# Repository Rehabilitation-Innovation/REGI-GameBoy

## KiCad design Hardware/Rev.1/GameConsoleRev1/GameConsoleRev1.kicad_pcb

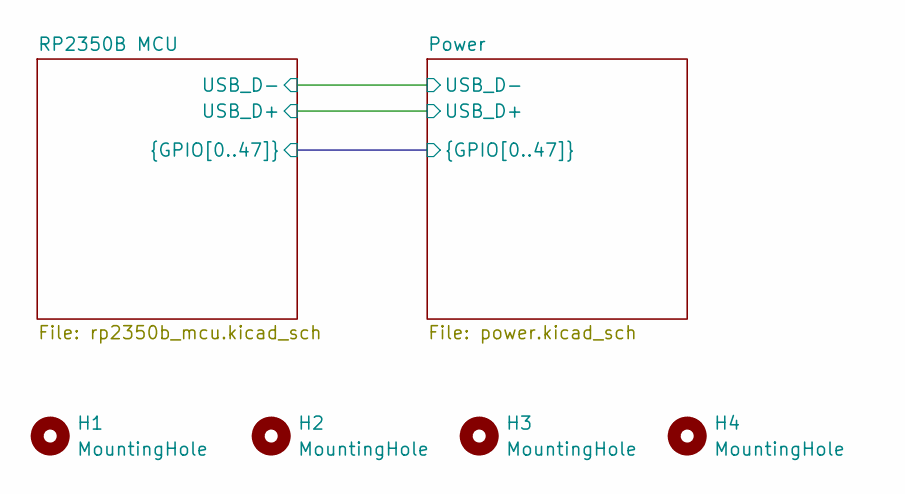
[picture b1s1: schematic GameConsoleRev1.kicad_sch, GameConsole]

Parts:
H1, H2, H3, H4: MountingHole; MountingHole_3.2mm_M3_Pad_Via

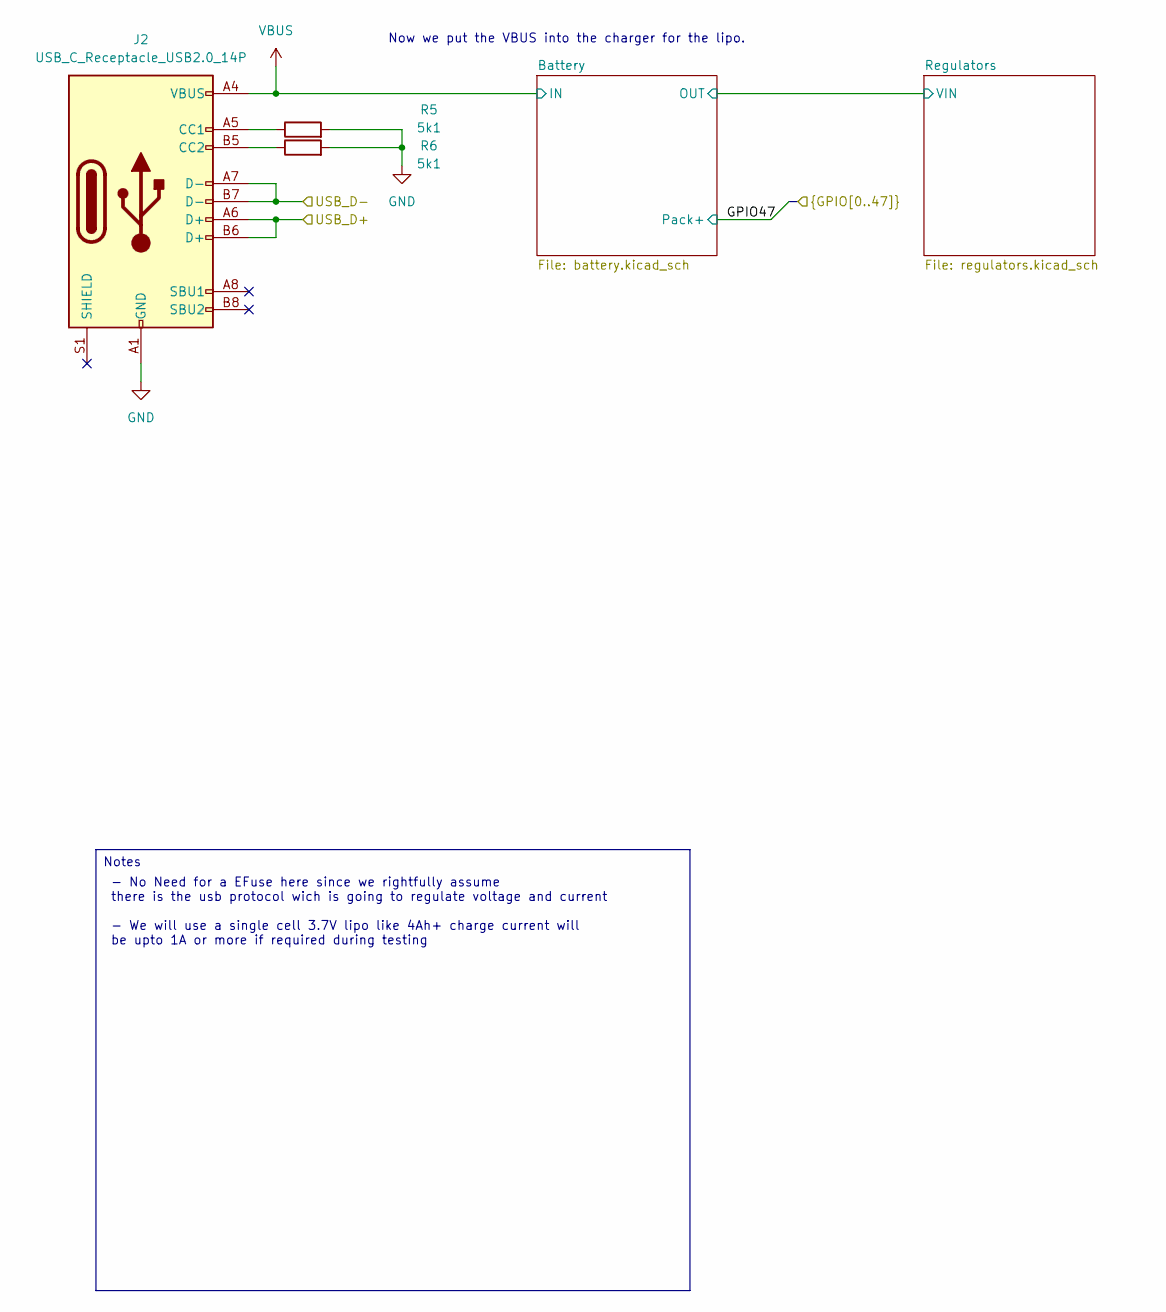
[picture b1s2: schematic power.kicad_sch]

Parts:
J2: USB_C_Receptacle_USB2.0_14P; USB_C_Receptacle_G-Switch_GT-USB-7010ASV; LCSC C2988369
R5, R6: 5k1; R_0402_1005Metric

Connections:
/Power/USB_D+: J2.A6 (D+), J2.B6 (D+); also elsewhere on the board
/Power/USB_D-: J2.A7 (D-), J2.B7 (D-); also elsewhere on the board
GND: J2.A1 (GND), J2.A12 (GND), J2.B1 (GND), J2.B12 (GND), R5.2, R6.2; also elsewhere on the board
unnamed: J2.A5 (CC1), R5.1
unnamed: J2.B5 (CC2), R6.1
VBUS: J2.A4 (VBUS), J2.A9 (VBUS), J2.B4 (VBUS), J2.B9 (VBUS); also elsewhere on the board

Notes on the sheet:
- No Need for a EFuse here since we rightfully assume there is the usb protocol wich is going to regulate voltage and current - We will use a single cell 3.7V lipo like 4Ah+ charge current will be upto 1A or more if required during testing
Now we put the VBUS into the charger for the lipo.
Notes

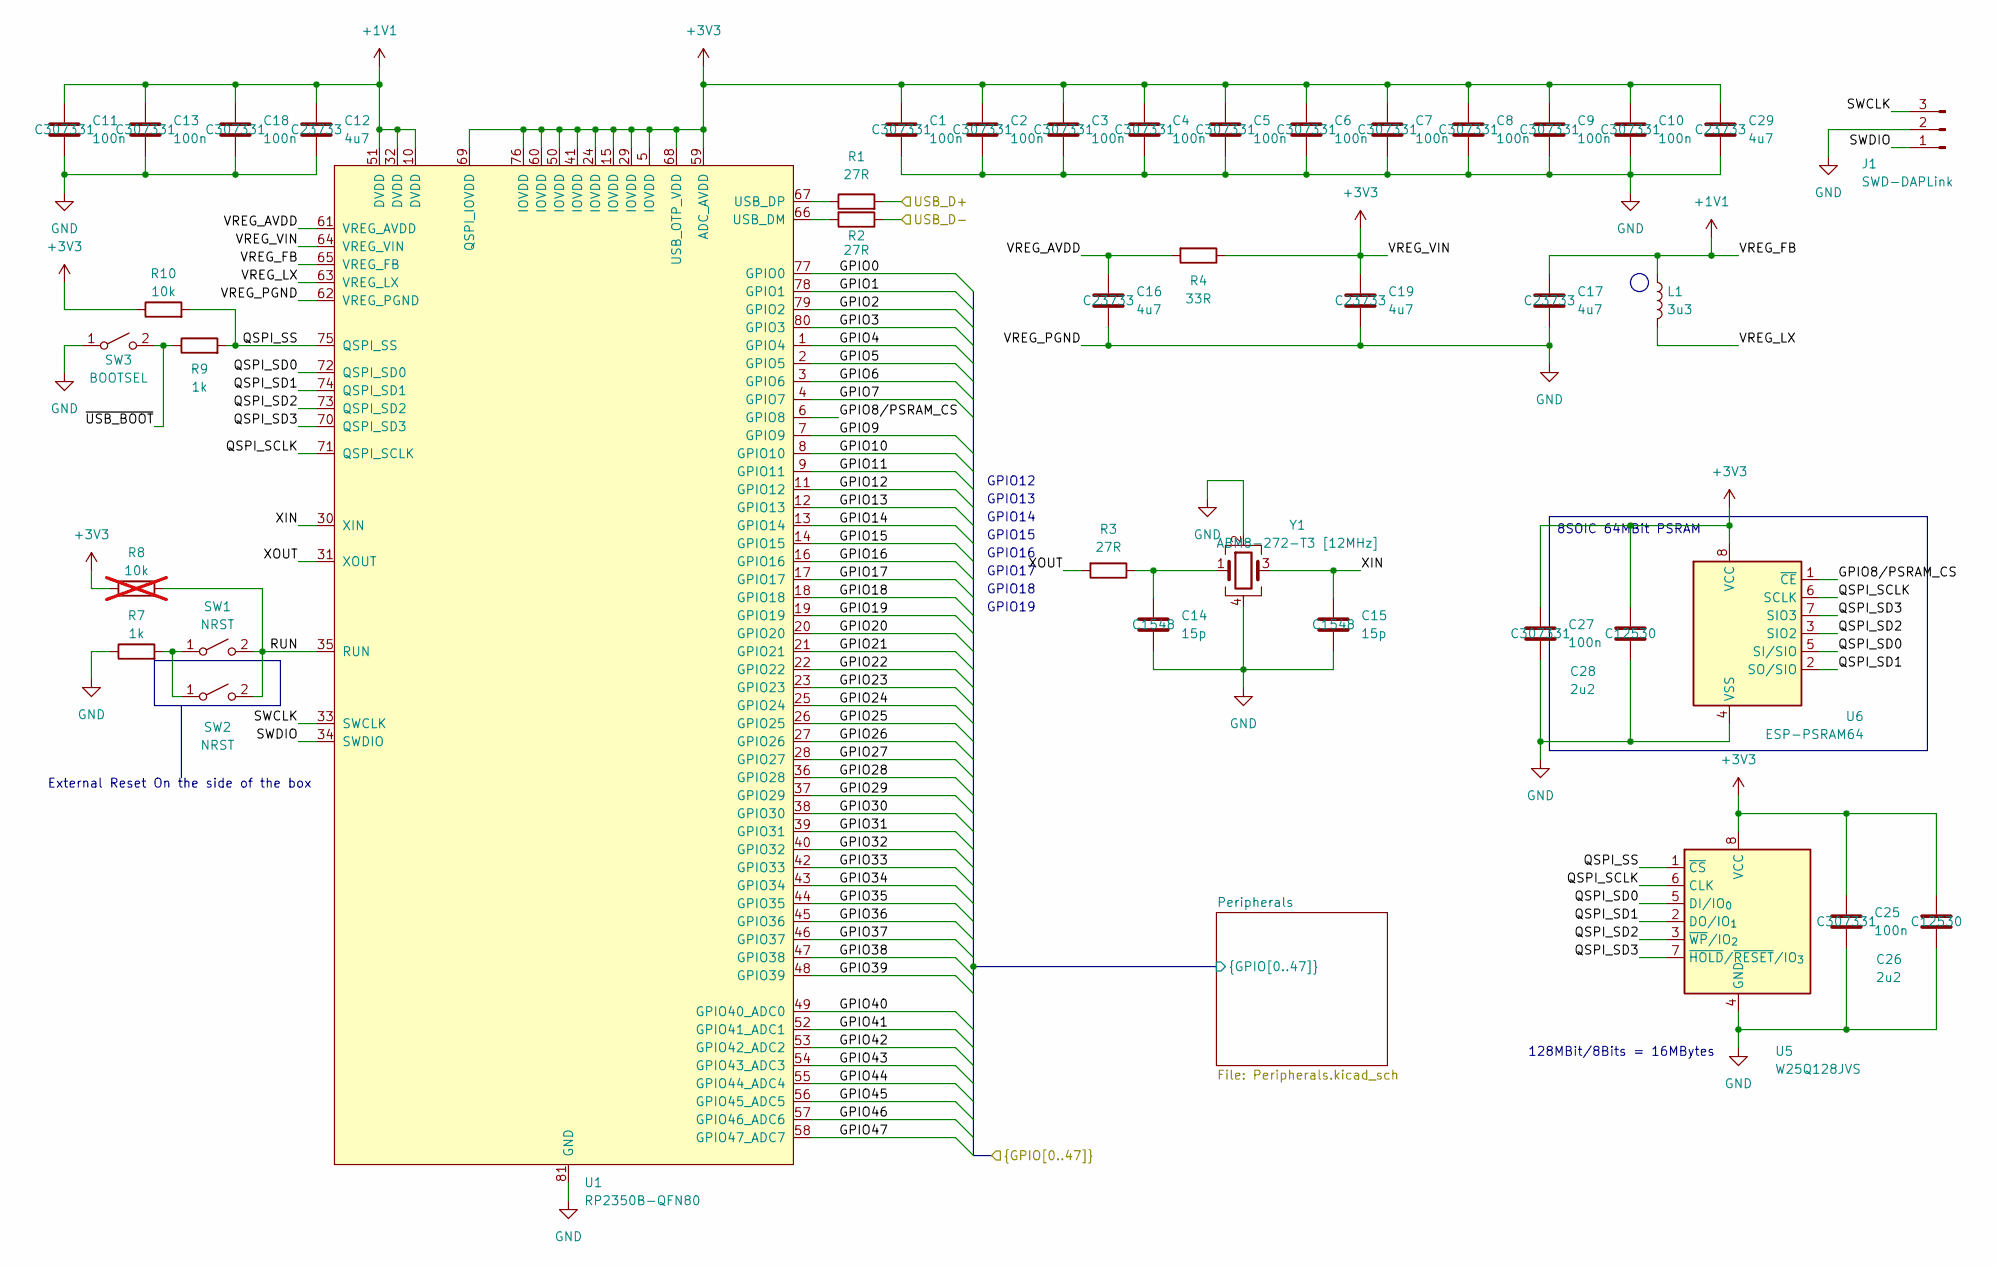
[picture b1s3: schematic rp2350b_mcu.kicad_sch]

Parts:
C1, C2, C3, C4, C5, C6, C7, C8, C9, C10, C11, C13, C18, C25, C27: 100n; C_0402_1005Metric; LCSC C307331
C12, C16, C17, C19, C29: 4u7; C_0402_1005Metric; LCSC C23733
C14, C15: 15p; C_0402_1005Metric; LCSC C1548
C26, C28: 2u2; C_0402_1005Metric; LCSC C12530
J1: SWD-DAPLink; PinHeader_1x03_P2.54mm_Vertical
L1: 3u3; AOTA-B201610S3R3-101-T; LCSC C42411119
R1, R2, R3: 27R; C_0402_1005Metric
R4: 33R; C_0402_1005Metric
R7, R9: 1k; R_0805_2012Metric
R8: 10k; R_0805_2012Metric; not fitted
R10: 10k; R_0805_2012Metric
SW1: NRST; SW_Push_1P1T_NO_Vertical_Wuerth_434133025816
SW2: NRST; SW_Tactile_SPST_Angled_PTS645Vx58-2LFS
SW3: BOOTSEL; SW_Push_1P1T_NO_Vertical_Wuerth_434133025816
U1: RP2350B-QFN80; RP2350B_QFN-80_EP_10.573x10.573_Pitch0.4mm; LCSC C42415655
U5: W25Q128JVS; SOIC-8_5.3x5.3mm_P1.27mm
U6: ESP-PSRAM64; SOIC-8_3.9x4.9mm_P1.27mm
Y1: ABM8-272-T3 [12MHz]; Crystal_SMD_3225-4Pin_3.2x2.5mm; LCSC C20625731

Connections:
+1V1: C11.1, C12.1, C13.1, C17.1, C18.1, L1.1, U1.10 (DVDD), U1.32 (DVDD), U1.51 (DVDD), U1.65 (VREG_FB)
+3V3: C1.1, C2.1, C3.1, C4.1, C5.1, C6.1, C7.1, C8.1, C9.1, C10.1, C19.1, C25.1, C26.1, C27.1, C28.1, C29.1, R4.1, R8.1, R10.1, U1.5 (IOVDD), U1.15 (IOVDD), U1.24 (IOVDD), U1.29 (IOVDD), U1.41 (IOVDD), U1.50 (IOVDD), U1.59 (ADC_AVDD), U1.60 (IOVDD), U1.64 (VREG_VIN), U1.68 (USB_OTP_VDD), U1.69 (QSPI_IOVDD), U1.76 (IOVDD), U5.8 (VCC), U6.8 (VCC); also elsewhere on the board
/Power/GPIO0: U1.77 (GPIO0); also elsewhere on the board
/Power/GPIO1: U1.78 (GPIO1); also elsewhere on the board
/Power/GPIO2: U1.79 (GPIO2); also elsewhere on the board
/Power/GPIO3: U1.80 (GPIO3); also elsewhere on the board
/Power/GPIO4: U1.1 (GPIO4); also elsewhere on the board
/Power/GPIO5: U1.2 (GPIO5); also elsewhere on the board
/Power/GPIO6: U1.3 (GPIO6); also elsewhere on the board
/Power/GPIO7: U1.4 (GPIO7); also elsewhere on the board
/Power/GPIO9: U1.7 (GPIO9); also elsewhere on the board
/Power/GPIO10: U1.8 (GPIO10); also elsewhere on the board
/Power/GPIO11: U1.9 (GPIO11); also elsewhere on the board
/Power/GPIO12: U1.11 (GPIO12); also elsewhere on the board
/Power/GPIO13: U1.12 (GPIO13); also elsewhere on the board
/Power/GPIO14: U1.13 (GPIO14); also elsewhere on the board
/Power/GPIO15: U1.14 (GPIO15); also elsewhere on the board
/Power/GPIO16: U1.16 (GPIO16); also elsewhere on the board
/Power/GPIO17: U1.17 (GPIO17); also elsewhere on the board
/Power/GPIO18: U1.18 (GPIO18); also elsewhere on the board
/Power/GPIO19: U1.19 (GPIO19); also elsewhere on the board
/Power/GPIO20: U1.20 (GPIO20); also elsewhere on the board
/Power/GPIO21: U1.21 (GPIO21); also elsewhere on the board
/Power/GPIO22: U1.22 (GPIO22); also elsewhere on the board
/Power/GPIO23: U1.23 (GPIO23); also elsewhere on the board
/Power/GPIO24: U1.25 (GPIO24); also elsewhere on the board
/Power/GPIO25: U1.26 (GPIO25); also elsewhere on the board
/Power/GPIO26: U1.27 (GPIO26); also elsewhere on the board
/Power/GPIO27: U1.28 (GPIO27); also elsewhere on the board
/Power/GPIO28: U1.36 (GPIO28); also elsewhere on the board
/Power/GPIO29: U1.37 (GPIO29); also elsewhere on the board
/Power/GPIO30: U1.38 (GPIO30); also elsewhere on the board
/Power/GPIO31: U1.39 (GPIO31); also elsewhere on the board
/Power/GPIO32: U1.40 (GPIO32); also elsewhere on the board
/Power/GPIO33: U1.42 (GPIO33); also elsewhere on the board
/Power/GPIO34: U1.43 (GPIO34); also elsewhere on the board
/Power/GPIO35: U1.44 (GPIO35); also elsewhere on the board
/Power/GPIO36: U1.45 (GPIO36); also elsewhere on the board
/Power/GPIO37: U1.46 (GPIO37); also elsewhere on the board
/Power/GPIO38: U1.47 (GPIO38); also elsewhere on the board
/Power/GPIO39: U1.48 (GPIO39); also elsewhere on the board
/Power/GPIO40: U1.49 (GPIO40_ADC0); also elsewhere on the board
/Power/GPIO41: U1.52 (GPIO41_ADC1); also elsewhere on the board
/Power/GPIO42: U1.53 (GPIO42_ADC2); also elsewhere on the board
/Power/GPIO43: U1.54 (GPIO43_ADC3); also elsewhere on the board
/Power/GPIO44: U1.55 (GPIO44_ADC4); also elsewhere on the board
/Power/GPIO45: U1.56 (GPIO45_ADC5); also elsewhere on the board
/Power/GPIO46: U1.57 (GPIO46_ADC6); also elsewhere on the board
/Power/GPIO47: U1.58 (GPIO47_ADC7); also elsewhere on the board
/Power/USB_D+: R1.2; also elsewhere on the board
/Power/USB_D-: R2.1; also elsewhere on the board
/RP2350B MCU/GPIO8/PSRAM_CS: U1.6 (GPIO8), U6.1 (~CE)
/RP2350B MCU/QSPI_SCLK: U1.71 (QSPI_SCLK), U5.6 (CLK), U6.6 (SCLK)
/RP2350B MCU/QSPI_SD0: U1.72 (QSPI_SD0), U5.5 (DI/IO_{0}), U6.5 (SI/SIO)
/RP2350B MCU/QSPI_SD1: U1.74 (QSPI_SD1), U5.2 (DO/IO_{1}), U6.2 (SO/SIO)
/RP2350B MCU/QSPI_SD2: U1.73 (QSPI_SD2), U5.3 (~WP/IO_{2}), U6.3 (SIO2)
/RP2350B MCU/QSPI_SD3: U1.70 (QSPI_SD3), U5.7 (~HOLD/~RESET/IO_{3}), U6.7 (SIO3)
/RP2350B MCU/QSPI_SS: R9.2, R10.2, U1.75 (QSPI_SS), U5.1 (~CS)
/RP2350B MCU/RUN: R8.2, SW1.2 (B), SW2.2 (B), U1.35 (RUN)
/RP2350B MCU/SWCLK: J1.3, U1.33 (SWCLK)
/RP2350B MCU/SWDIO: J1.1, U1.34 (SWDIO)
/RP2350B MCU/VREG_AVDD: C16.1, R4.2, U1.61 (VREG_AVDD)
/RP2350B MCU/VREG_LX: L1.2, U1.63 (VREG_LX)
/RP2350B MCU/XIN: C15.1, U1.30 (XIN), Y1.3
/RP2350B MCU/XOUT: R3.2, U1.31 (XOUT)
/RP2350B MCU/~USB_BOOT: R9.1, SW3.2 (B)
GND: C1.2, C2.2, C3.2, C4.2, C5.2, C6.2, C7.2, C8.2, C9.2, C10.2, C11.2, C12.2, C13.2, C14.2, C15.2, C16.2, C17.2, C18.2, C19.2, C25.2, C26.2, C27.2, C28.2, C29.2, J1.2, R7.1, SW3.1 (A), U1.62 (VREG_PGND), U1.81 (GND), U5.4 (GND), U6.4 (VSS), Y1.2, Y1.4; also elsewhere on the board
unnamed: C14.1, R3.1, Y1.1
unnamed: R7.2, SW1.1 (A), SW2.1 (A)
unnamed: R2.2, U1.66 (USB_DM)
unnamed: R1.1, U1.67 (USB_DP)

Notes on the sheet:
GPIO15
GPIO19
GPIO16
GPIO14
GPIO17
128MBit/8Bits = 16MBytes
GPIO18
External Reset On the side of the box
GPIO12
GPIO13
8SOIC 64MBit PSRAM

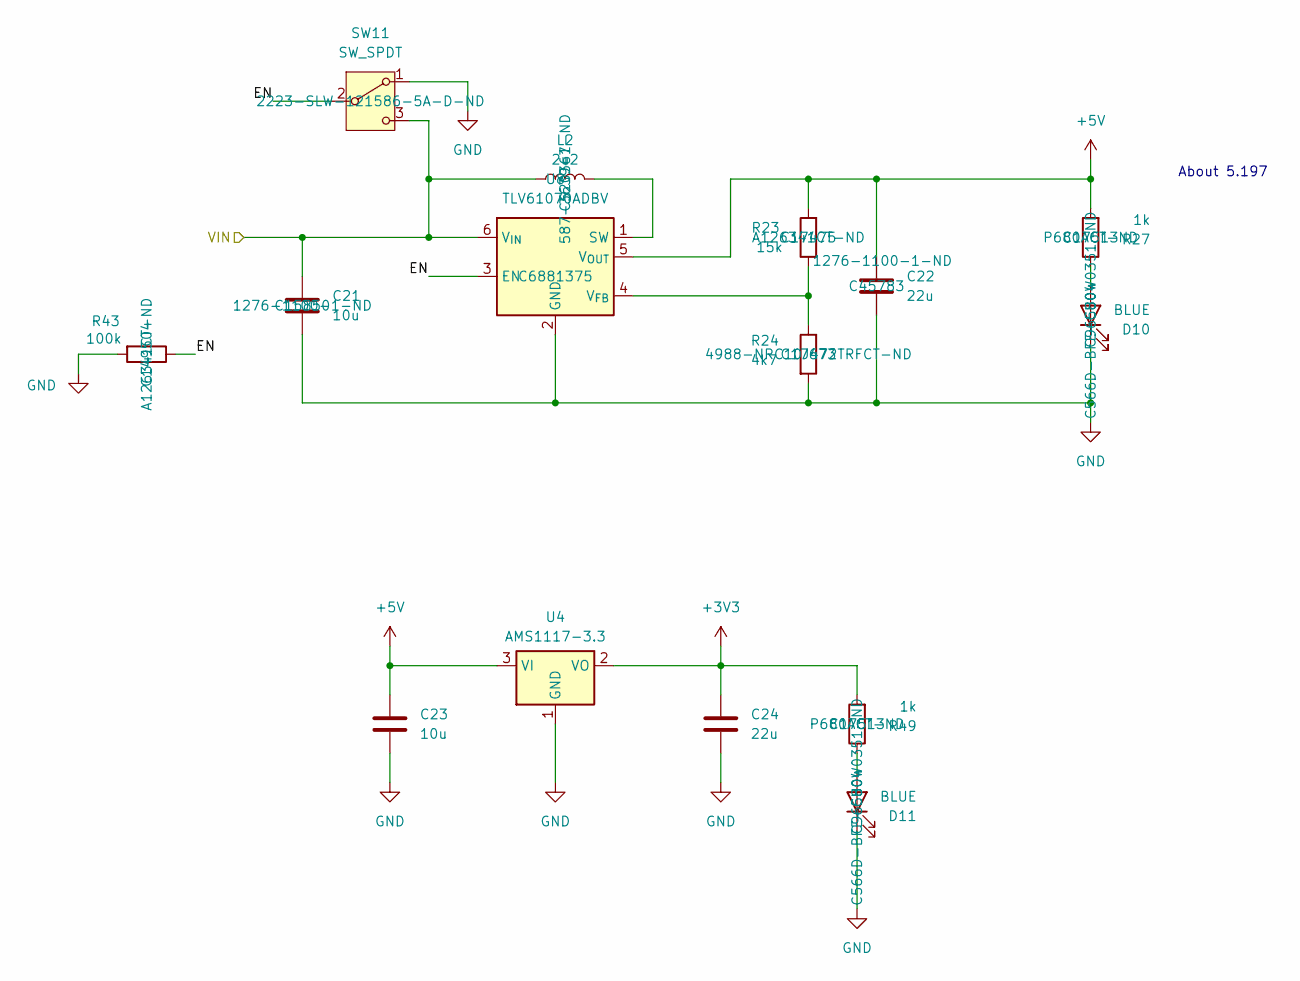
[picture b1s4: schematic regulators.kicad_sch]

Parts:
C21: 10u; C_0805_2012Metric; LCSC C15850
C22: 22u; C_0805_2012Metric; LCSC C45783
C23: 10u; C_1206_3216Metric; LCSC C13585
C24: 22u; C_1206_3216Metric; LCSC C12891
D10, D11: BLUE; LED_0603_1608Metric; LCSC C965804
L2: 2u2; Ceaiya SMD,6x6mm CR6028-2R2N; LCSC C520367
R23: 15k; R_0805_2012Metric; LCSC C17475
R24: 4k7; R_0805_2012Metric; LCSC C17673
R27, R49: 1k; R_0805_2012Metric; LCSC C17513
R43: 100k; R_0805_2012Metric; LCSC C149504
SW11: SW_SPDT; SW_SLW-121586-5A-D
U4: AMS1117-3.3; SOT-223-3_TabPin2; LCSC C6186
U8: TLV61070ADBV; SOT-23-6; LCSC C6881375

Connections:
+3V3: C24.1, R49.2, U4.2 (VO); also elsewhere on the board
+5V: C22.1, C23.1, R23.2, R27.2, U4.3 (VI), U8.5 (V_{OUT}); also elsewhere on the board
/Power/Battery/OUT: C21.1, L2.1, SW11.3 (C), U8.6 (V_{IN}); also elsewhere on the board
/Power/Regulators/EN: R43.1, SW11.2 (B), U8.3 (EN)
GND: C21.2, C22.2, C23.2, C24.2, D10.1 (K), D11.1 (K), R24.2, R43.2, SW11.1 (A), U4.1 (GND), U8.2 (GND); also elsewhere on the board
unnamed: D10.2 (A), R27.1
unnamed: D11.2 (A), R49.1
unnamed: L2.2, U8.1 (SW)
unnamed: R23.1, R24.1, U8.4 (V_{FB})

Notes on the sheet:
About 5.197

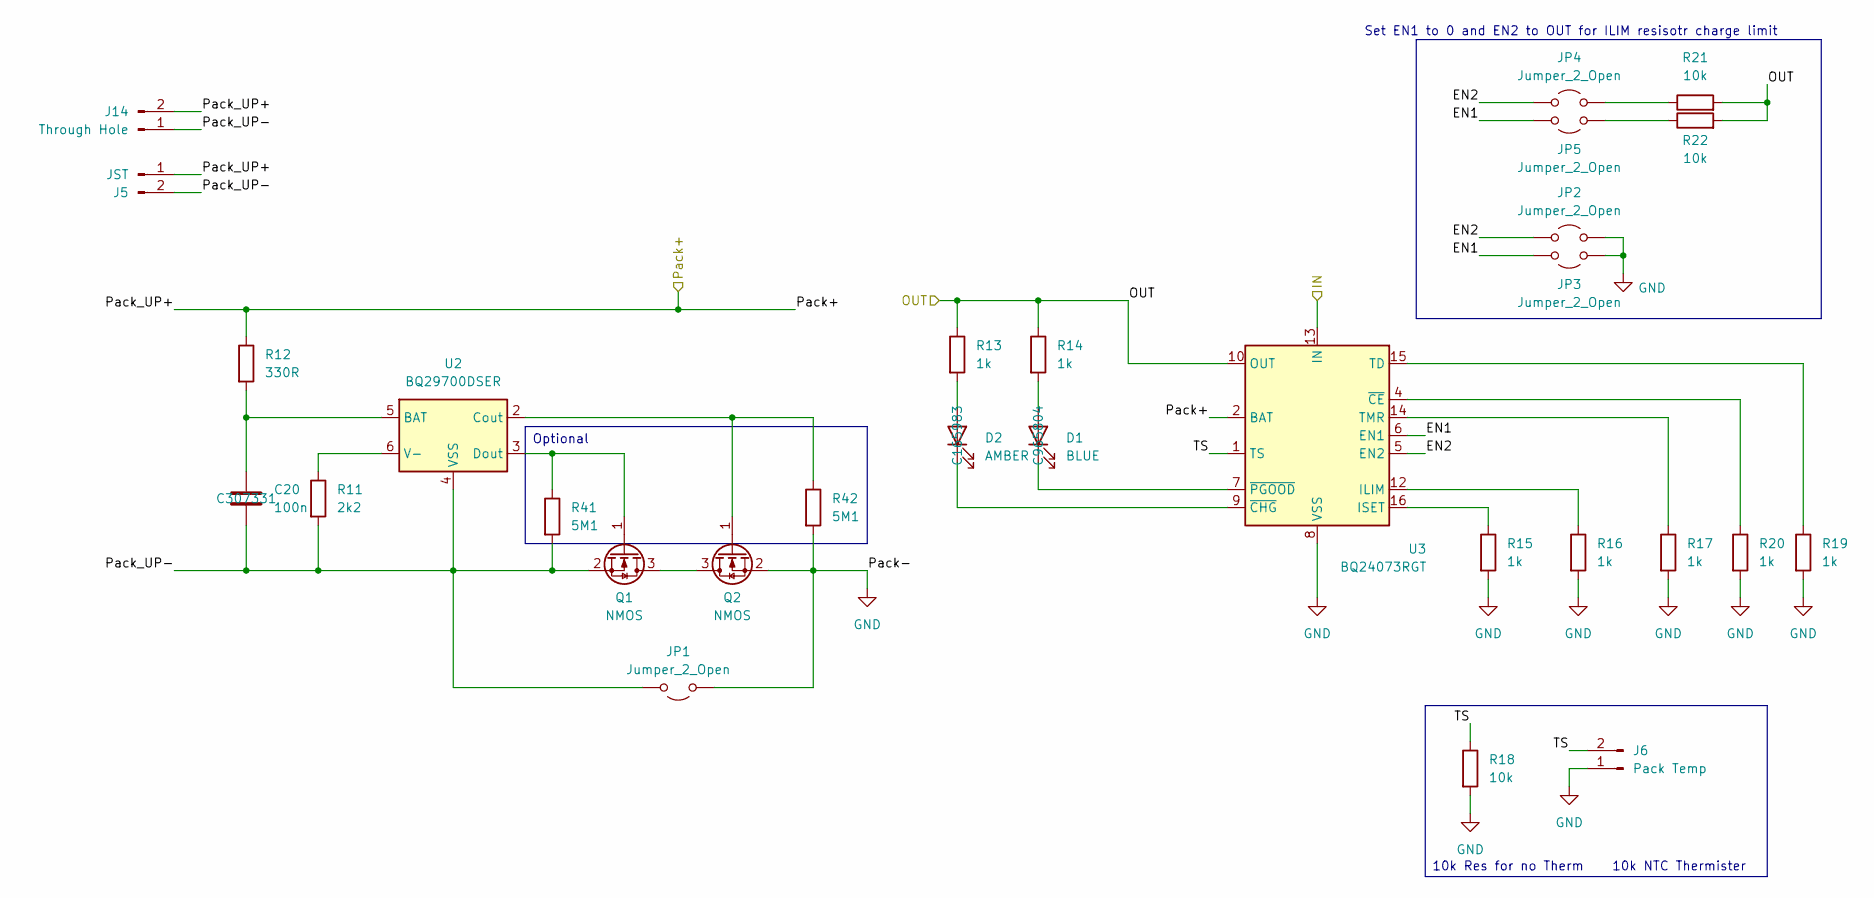
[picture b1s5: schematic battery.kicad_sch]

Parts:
C20: 100n; C_0402_1005Metric; LCSC C307331
D1: BLUE; LED_0603_1608Metric; LCSC C965804
D2: AMBER; LED_0603_1608Metric; LCSC C165983
J5: JST; JST_PH_B2B-PH-K_1x02_P2.00mm_Vertical
J6: Pack Temp; PinHeader_1x02_P2.54mm_Vertical
J14: Through Hole; PinHeader_1x02_P2.54mm_Vertical
JP1, JP2, JP3, JP4, JP5: Jumper_2_Open; SolderJumper-2_P1.3mm_Open_TrianglePad1.0x1.5mm
Q1, Q2: NMOS; SOT-23; LCSC C427390
R11: 2k2; R_0805_2012Metric
R12: 330R; R_0805_2012Metric
R13, R14, R15, R16, R17, R19, R20: 1k; R_0805_2012Metric
R18: 10k; R_0805_2012Metric
R21, R22: 10k; R_0402_1005Metric
R41, R42: 5M1; R_0805_2012Metric
U2: BQ29700DSER; WSON-6_1.5x1.5mm_P0.5mm; LCSC C183096
U3: BQ24073RGT; VQFN-16-1EP_3x3mm_P0.5mm_EP1.6x1.6mm; LCSC C15220

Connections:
/Power/Battery/EN1: JP3.2 (B), JP5.2 (B), U3.6 (EN1)
/Power/Battery/EN2: JP2.1 (A), JP4.1 (A), U3.5 (EN2)
/Power/Battery/OUT: R13.1, R14.1, R21.2, R22.2, U3.10 (OUT), U3.11 (OUT); also elsewhere on the board
/Power/Battery/Pack_UP-: C20.2, J5.2, J14.1, JP1.2 (B), Q1.2 (S), R11.2, R41.2, U2.4 (VSS)
/Power/Battery/TS: J6.2, R18.1, U3.1 (TS)
/Power/GPIO47: J5.1, J14.2, R12.1, U3.2 (BAT), U3.3 (BAT); also elsewhere on the board
GND: J6.1, JP1.1 (A), JP2.2 (B), JP3.1 (A), Q2.2 (S), R15.2, R16.2, R17.2, R18.2, R19.2, R20.2, R42.2, U3.8 (VSS), U3.17 (VSS); also elsewhere on the board
unnamed: D1.2 (A), R14.2
unnamed: D1.1 (K), U3.7 (~PGOOD)
unnamed: D2.2 (A), R13.2
unnamed: D2.1 (K), U3.9 (~CHG)
unnamed: JP4.2 (B), R21.1
unnamed: JP5.1 (A), R22.1
unnamed: Q1.3 (D), Q2.3 (D)
unnamed: Q1.1 (G), R41.1, U2.3 (Dout)
unnamed: Q2.1 (G), R42.1, U2.2 (Cout)
unnamed: C20.1, R12.2, U2.5 (BAT)
unnamed: R11.1, U2.6 (V-)
unnamed: R16.1, U3.12 (ILIM)
unnamed: R15.1, U3.16 (ISET)
unnamed: R19.1, U3.15 (TD)
unnamed: R17.1, U3.14 (TMR)
unnamed: R20.1, U3.4 (~CE)
VBUS: U3.13 (IN); also elsewhere on the board

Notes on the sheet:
10k NTC Thermister
Set EN1 to 0 and EN2 to OUT for ILIM resisotr charge limit
10k Res for no Therm
Optional

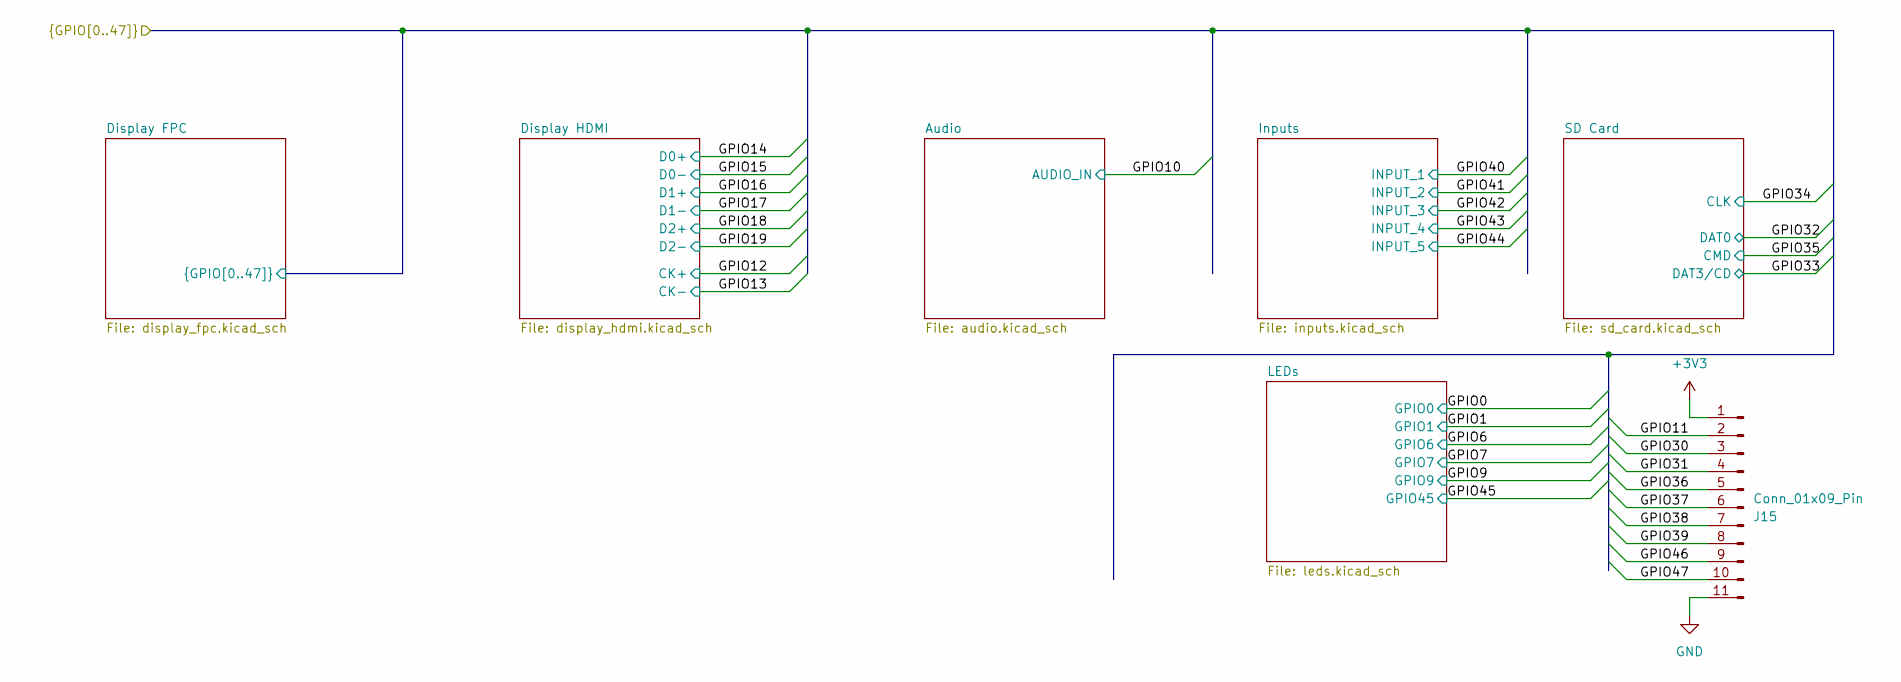
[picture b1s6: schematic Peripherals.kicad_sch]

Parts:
J15: Conn_01x09_Pin; PinSocket_1x11_P2.54mm_Vertical

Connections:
+3V3: J15.1; also elsewhere on the board
/Power/GPIO11: J15.2; also elsewhere on the board
/Power/GPIO30: J15.3; also elsewhere on the board
/Power/GPIO31: J15.4; also elsewhere on the board
/Power/GPIO36: J15.5; also elsewhere on the board
/Power/GPIO37: J15.6; also elsewhere on the board
/Power/GPIO38: J15.7; also elsewhere on the board
/Power/GPIO39: J15.8; also elsewhere on the board
/Power/GPIO46: J15.9; also elsewhere on the board
/Power/GPIO47: J15.10; also elsewhere on the board
GND: J15.11; also elsewhere on the board

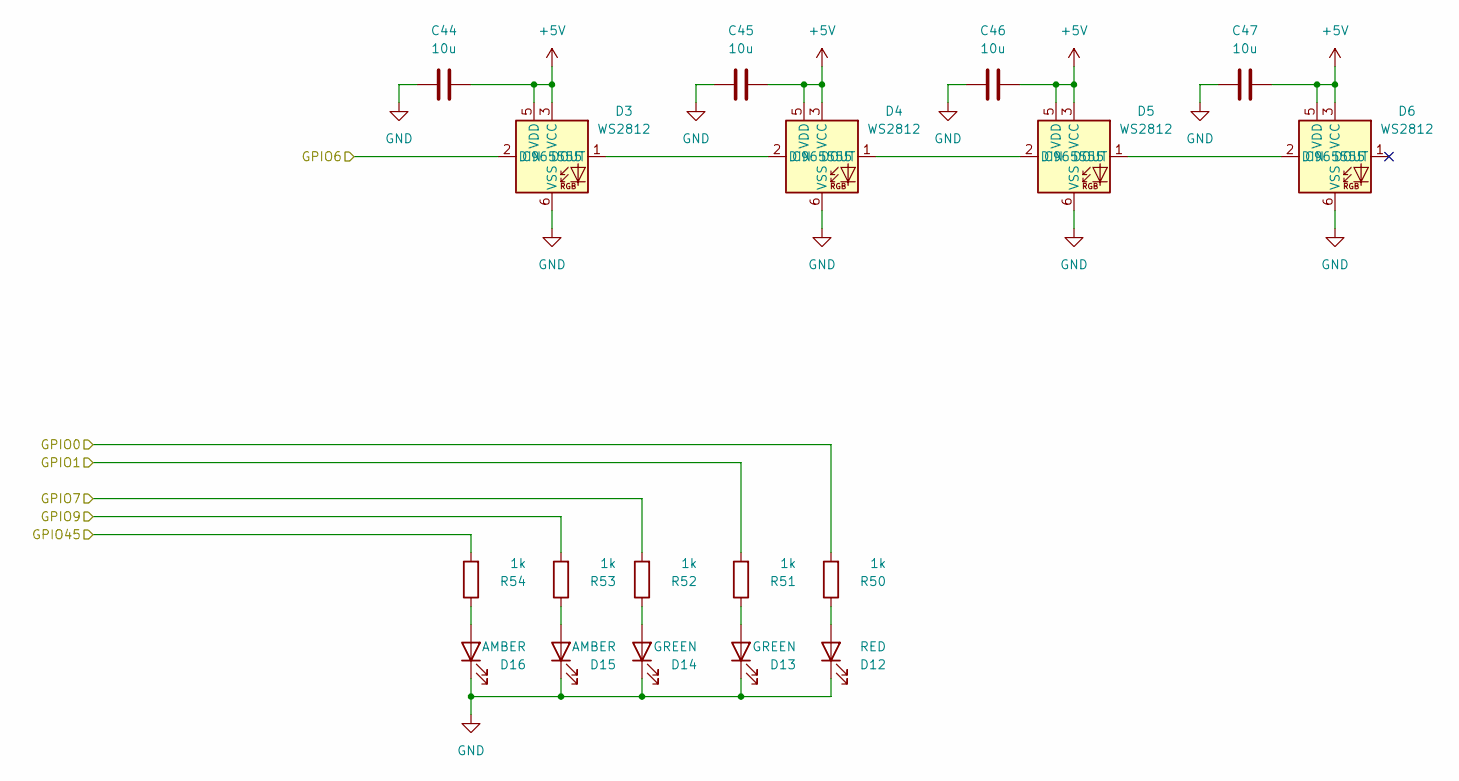
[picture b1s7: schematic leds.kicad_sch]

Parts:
C44, C45, C46, C47: 10u; C_0402_1005Metric; LCSC C15525
D3, D4, D5, D6: WS2812; LED_WS2812_PLCC6_5.0x5.0mm_P1.6mm; LCSC C965555
D12: RED; LED_0603_1608Metric; LCSC C965804
D13, D14: GREEN; LED_0603_1608Metric; LCSC C965804
D15, D16: AMBER; LED_0603_1608Metric; LCSC C965804
R50, R51, R52, R53, R54: 1k; R_0805_2012Metric; LCSC C17513

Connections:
+5V: C44.1, C45.1, C46.1, C47.1, D3.3 (VCC), D3.5 (VDD), D4.3 (VCC), D4.5 (VDD), D5.3 (VCC), D5.5 (VDD), D6.3 (VCC), D6.5 (VDD); also elsewhere on the board
/Power/GPIO0: R50.2; also elsewhere on the board
/Power/GPIO1: R51.2; also elsewhere on the board
/Power/GPIO6: D3.2 (DIN); also elsewhere on the board
/Power/GPIO7: R52.2; also elsewhere on the board
/Power/GPIO9: R53.2; also elsewhere on the board
/Power/GPIO45: R54.2; also elsewhere on the board
GND: C44.2, C45.2, C46.2, C47.2, D3.6 (VSS), D4.6 (VSS), D5.6 (VSS), D6.6 (VSS), D12.1 (K), D13.1 (K), D14.1 (K), D15.1 (K), D16.1 (K); also elsewhere on the board
unnamed: D3.1 (DOUT), D4.2 (DIN)
unnamed: D4.1 (DOUT), D5.2 (DIN)
unnamed: D5.1 (DOUT), D6.2 (DIN)
unnamed: D12.2 (A), R50.1
unnamed: D13.2 (A), R51.1
unnamed: D14.2 (A), R52.1
unnamed: D15.2 (A), R53.1
unnamed: D16.2 (A), R54.1

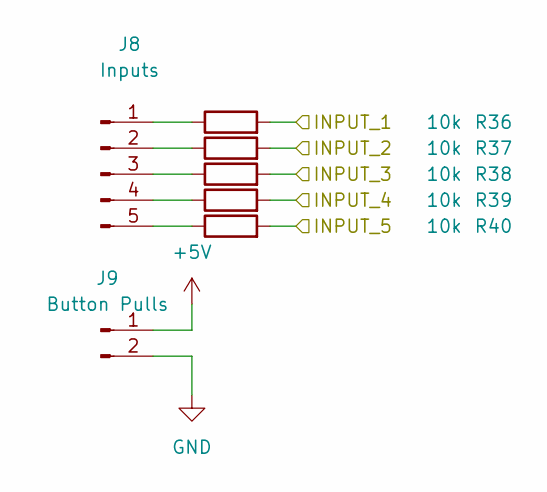
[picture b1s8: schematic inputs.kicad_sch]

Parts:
J8: Inputs; PinHeader_1x05_P2.54mm_Vertical
J9: Button Pulls; PinHeader_1x02_P2.54mm_Vertical
R36, R37, R38, R39, R40: 10k; R_0402_1005Metric

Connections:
+5V: J9.1; also elsewhere on the board
/Power/GPIO40: R36.2; also elsewhere on the board
/Power/GPIO41: R37.2; also elsewhere on the board
/Power/GPIO42: R38.2; also elsewhere on the board
/Power/GPIO43: R39.2; also elsewhere on the board
/Power/GPIO44: R40.2; also elsewhere on the board
GND: J9.2; also elsewhere on the board
unnamed: J8.1, R36.1
unnamed: J8.2, R37.1
unnamed: J8.3, R38.1
unnamed: J8.4, R39.1
unnamed: J8.5, R40.1

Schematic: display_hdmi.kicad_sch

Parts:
J7: HDMI_A; HDMI_A_Molex_208658-1001_Horizontal
R25, R26, R28, R29, R30, R31, R32, R33: 220R; R_0402_1005Metric
R34: 10k; R_0805_2012Metric; not fitted
R35: 10k; R_0805_2012Metric

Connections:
+5V: R34.2; also elsewhere on the board
/Power/GPIO12: R32.1; also elsewhere on the board
/Power/GPIO13: R33.1; also elsewhere on the board
/Power/GPIO14: R30.1; also elsewhere on the board
/Power/GPIO15: R31.1; also elsewhere on the board
/Power/GPIO16: R28.1; also elsewhere on the board
/Power/GPIO17: R29.1; also elsewhere on the board
/Power/GPIO18: R25.1; also elsewhere on the board
/Power/GPIO19: R26.1; also elsewhere on the board
/RP2350B MCU/Peripherals/Display HDMI/+5V_HDMI: J7.18 (+5V), R34.1, R35.1
GND: J7.2 (D2S), J7.5 (D1S), J7.8 (D0S), J7.11 (CKS), J7.17 (GND), J7.SH; also elsewhere on the board
unnamed: J7.10 (CK+), R32.2
unnamed: J7.12 (CK-), R33.2
unnamed: J7.7 (D0+), R30.2
unnamed: J7.9 (D0-), R31.2
unnamed: J7.4 (D1+), R28.2
unnamed: J7.6 (D1-), R29.2
unnamed: J7.1 (D2+), R25.2
unnamed: J7.3 (D2-), R26.2
unnamed: J7.19 (HPD), R35.2

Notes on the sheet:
https://cdn-learn.adafruit.com/assets/assets/000/111/261/original/components_schem.png?1651496250

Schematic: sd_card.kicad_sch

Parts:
C32, C43: 22u; C_0805_2012Metric; LCSC C45783
J13: Micro_SD_Card; microSD_HC_Molex_47219-2001

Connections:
+3V3: C32.1, C43.1, J13.4 (VDD); also elsewhere on the board
/Power/GPIO32: J13.7 (DAT0); also elsewhere on the board
/Power/GPIO33: J13.2 (DAT3/CD); also elsewhere on the board
/Power/GPIO34: J13.5 (CLK); also elsewhere on the board
/Power/GPIO35: J13.3 (CMD); also elsewhere on the board
GND: C32.2, C43.2, J13.6 (VSS); also elsewhere on the board

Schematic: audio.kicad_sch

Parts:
C33, C34, C35, C37, C41, C42: 1u; C_0402_1005Metric; LCSC C52923
C36, C40: 100n; C_0402_1005Metric; LCSC C307331
C38, C39: 10u; C_0402_1005Metric; LCSC C15525
FB3, FB4, FB5, FB6: 600R@100MHz; R_0805_2012Metric; LCSC C1017
J3: L Channel; PinSocket_1x02_P2.54mm_Vertical
J4: R Channel; PinSocket_1x02_P2.54mm_Vertical
R47, R48: 10k; R_0402_1005Metric
RV1: R_Potentiometer; RES3_91A_TTE
SW5: SW_SPDT; SW_SPDT_PCM12
U10, U11: PAM8302AAS; MSOP-8_3x3mm_P0.65mm

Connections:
+5V: C33.1, C36.1, C37.1, C38.1, C39.1, C40.1, R48.2, U10.6 (VDD), U11.6 (VDD); also elsewhere on the board
/Power/GPIO10: RV1.1; also elsewhere on the board
/RP2350B MCU/Peripherals/Audio/AIN+: C34.1, C41.1, RV1.2
/RP2350B MCU/Peripherals/Audio/L_CHAN: FB3.2, J3.2
/RP2350B MCU/Peripherals/Audio/L_CHAN-: FB4.2, J3.1
/RP2350B MCU/Peripherals/Audio/R_CHAN: FB5.2, J4.2
/RP2350B MCU/Peripherals/Audio/R_CHAN-: FB6.2, J4.1
/RP2350B MCU/Peripherals/Audio/~SD: SW5.2 (B), U10.1 (~SD), U11.1 (~SD)
GND: C33.2, C35.1, C36.2, C37.2, C38.2, C39.2, C40.2, C42.1, R47.2, RV1.3, U10.7 (GND), U11.7 (GND); also elsewhere on the board
unnamed: R48.1, SW5.1 (A)
unnamed: R47.1, SW5.3 (C)
unnamed: C34.2, U10.3 (IN+)
unnamed: C35.2, U10.4 (IN-)
unnamed: FB3.1, U10.5 (OUT+)
unnamed: FB4.1, U10.8 (OUT-)
unnamed: C41.2, U11.3 (IN+)
unnamed: C42.2, U11.4 (IN-)
unnamed: FB5.1, U11.5 (OUT+)
unnamed: FB6.1, U11.8 (OUT-)

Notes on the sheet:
Mono Audio because no point in stereo
Solder the speaker wires; Dont mess with connectors.

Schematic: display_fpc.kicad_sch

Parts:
C30, C31: 22u; C_0805_2012Metric; LCSC C45783
J10: Conn_01x40; Hirose_FH12-40S-0.5SH_1x40-1MP_P0.50mm_Horizontal; LCSC C19273935
J11, J12: Conn_01x08_Pin; PinHeader_1x08_P2.54mm_Vertical
JP6, JP7, JP8, JP9, JP10, JP11: Jumper_2_Open; SolderJumper-2_P1.3mm_Open_TrianglePad1.0x1.5mm
Q3: NTR1P02T1G; SOT-23; LCSC C129192
R44, R45, R46: 2R; R_0603_1608Metric

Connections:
+3V3: C30.1, C31.1, J10.6, J10.7, J10.12, J10.33, J12.7, JP9.2 (B), JP10.2 (B), JP11.2 (B); also elsewhere on the board
/Power/GPIO2: J10.8, J12.6; also elsewhere on the board
/Power/GPIO3: J10.10, J12.5; also elsewhere on the board
/Power/GPIO4: J10.11, J12.4; also elsewhere on the board
/Power/GPIO5: J10.15, J12.3; also elsewhere on the board
/Power/GPIO20: J10.25, J11.8; also elsewhere on the board
/Power/GPIO21: J10.26, J11.7; also elsewhere on the board
/Power/GPIO22: J10.27, J11.6; also elsewhere on the board
/Power/GPIO23: J10.28, J11.5; also elsewhere on the board
/Power/GPIO24: J10.29, J11.4; also elsewhere on the board
/Power/GPIO25: J10.30, J11.3; also elsewhere on the board
/Power/GPIO26: J10.31, J11.2; also elsewhere on the board
/Power/GPIO27: J10.32, J11.1; also elsewhere on the board
/Power/GPIO28: J12.2, Q3.1 (G); also elsewhere on the board
/Power/GPIO29: J10.9, J12.1; also elsewhere on the board
/RP2350B MCU/Peripherals/Display FPC/IM0: J10.38, JP6.1 (A), JP9.1 (A)
/RP2350B MCU/Peripherals/Display FPC/IM1: J10.39, JP7.1 (A), JP10.1 (A)
/RP2350B MCU/Peripherals/Display FPC/IM2: J10.40, JP8.1 (A), JP11.1 (A)
/RP2350B MCU/Peripherals/Display FPC/LED_GND: Q3.2 (S), R44.2, R45.2, R46.2
GND: C30.2, C31.2, J10.5, J10.13, J10.16, J10.17, J10.18, J10.19, J10.20, J10.21, J10.22, J10.23, J10.24, J10.37, J12.8, JP6.2 (B), JP7.2 (B), JP8.2 (B), Q3.3 (D); also elsewhere on the board
unnamed: J10.34, R46.1
unnamed: J10.35, R45.1
unnamed: J10.36, R44.1
